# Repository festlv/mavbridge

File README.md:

MAVBridge
------------------

MAVBridge is stand-alone ESP8266 based serial MAVLink <-> wireless bridge. It is compatible
with MAVLink v1.0 specification and 

Compatibility has been tested with:

* Pixhawk hardware (PX4 and ArduPilot flight stacks)
* APMPlanner
* MissionPlanner
* DroidTower
* qGroundcontrol
* MAVProxy

Device has built-in web interface for configuration and status.

At the moment, only UDP transport layer is supported. TCP support is
work-in-progress (functionality is there, but ESP runs out of RAM and crashes
when transmitting a lot of data).

As for performance- UDP has been successfully tested at 921600 baud rate and
almost 70 KiB/s data rate without packet-loss (depends on number of WiFi
networks around device , of course).

Configuration interface
--------------------------------

Index/status page:

Settings:

Building firmware
-------------------

Prerequisites for building:
* https://github.com/pfalcon/esp-open-sdk with Espressif IOT SDK 1.5.2
* Sming framework: https://github.com/SmingHub/Sming/releases/tag/2.1.0

Assuming the requirements above are satisfied, building is as simple as:

    cd firmware
    make

Hardware
-----------

Hardware is designed using Kicad and the design is available in hardware
folder.

Testing
--------------

Python scripts that automatically test performance and stability of the
MAVBridge are available in `throughput-test/`. Tests require pymavlink.

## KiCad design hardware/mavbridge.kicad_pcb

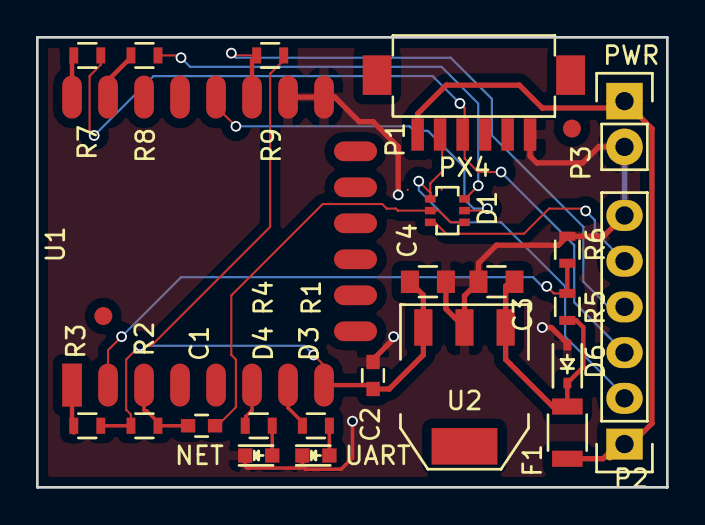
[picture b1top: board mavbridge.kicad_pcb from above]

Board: 2 copper layers, 35.0 x 25.0 mm, 23 parts (0 on the bottom side), 20 nets.

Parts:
C1, C2: 0.1uF; C_0603
C3, C4: 22uF; C_0805
D1: BAT54TW; SOT-363
D3: UART; LED-0603
D4: NET; LED-0603
D6: D_Schottky; SOD-323
F1: F_Small; R_1206
P1: PX4; DF13-6
P2: DEBUG; Pin_Header_Straight_1x06
P3: PWR; Pin_Header_Straight_1x02
R1, R4, R7, R8: 120R; R_0603
R2, R3, R5, R6, R9: 10K; R_0603
U1: ESP-12E
U2: AP7361; SOT-223

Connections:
+3V3: C2.1, C4.1, R2.2, R3.2, R9.2, U1.8, U2.3
+5V: C3.1, D6.1, F1.2, R5.2, U2.1
/DBG_TX: P2.4, R9.1, U1.17
/GPIO0: D1.2, U1.18
/GPIO12: R4.2, U1.6
/GPIO13: R1.2, U1.7
DTR: D1.6, P2.5
GND: C2.2, C3.2, C4.2, D3.1, D4.1, D6.2, P1.6, P2.6, P3.2, R6.1, U1.15, U1.16, U2.2
unnamed: C1.1, R2.1, U1.3
unnamed: C1.2, D1.1, D1.5
unnamed: D1.3, R8.1
unnamed: D3.2, R1.1
unnamed: D4.2, R4.1
unnamed: R3.1, U1.1
unnamed: R5.1, R6.2, U1.2
unnamed: R7.2, U1.22
unnamed: R8.2, U1.21
RXD: D1.4, P1.2, P2.2
TXD: P1.3, P2.3, R7.1
VPP: F1.1, P1.1, P2.1, P3.1

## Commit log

2015-12-03 Adds first working version. Requires ESP IOT-SDK 1.5.0.
2015-12-05 Moves firmware to separate folder.
2015-12-05 Moves mavlink submodule to firmware directory.
2015-12-07 Adds rev 1 hardware.
2015-12-09 Initial configuration interface.
2015-12-09 Fixes parameter saving/restoring.
    Also AP name now contains MAC address.
2015-12-10 Configuration interface is now functional.
2015-12-11 Prints debug output to UART1 (on GPIO2).
2015-12-14 Removes debug serial, custom UART1 driver not stable.
2015-12-14 Adds silkscreen pinout for HW layout
2015-12-14 Adds OTA SW update using rBoot.
2015-12-14 Split the web config part in three parts: status, settings and networks.
2015-12-17 Multiple changes to web configuration interface.
    Adds:
    * Uptime reporting,
    * AP security settings.
    * Debug information enable/disable.
2016-01-02 Adds component fields
2016-01-16 Changes to firmware:
    * Blinks UART/NET LEDs;
    * Increases UART receive timer frequency;
    * Loads app settings before testing for existence;
2016-01-17 Adds feature which resets parameters when GPIO is held low for 3 seconds.
2016-01-21 Ordered rev2 hardware.
2016-02-19 TCP in progress.
2016-02-28 Updates BOM from Maritex
2016-02-28 Adds pricing information.
2016-03-06 Adds MAVLink spoofer tool
2016-03-06 Fixes issue #2, reboots after making changes to settings.
2016-03-06 WIP on TCP transport protocol. Works, but runs out of memory at fast datarates.
2016-03-21 Moves implementation of ApplicationSettingsStorage out of header.
2016-03-21 More work on TCP option. Stable up to 7KiB/s :(
2016-03-25 Release v2 firmware.
2016-03-25 MAVLink decoding does not depend on message definitions anymore.
2016-03-26 Throughput test only counts successfully received messages.
2016-03-26 Adds automatic throughput tests, UI screenshots.
2016-03-26 Readme update update
2016-03-26 Less numbers, more features.
2016-03-27 Release version v3.
2016-03-27 Adds license.
2016-03-27 Adds schematics in PDF format.
2016-04-16 Adds prebuilt binaries and instructions on flashing.
2017-05-23 Small changes to build for Sming 3.2.0.
2017-05-23 Updating prebuilt binaries built against Sming 3.2.0
